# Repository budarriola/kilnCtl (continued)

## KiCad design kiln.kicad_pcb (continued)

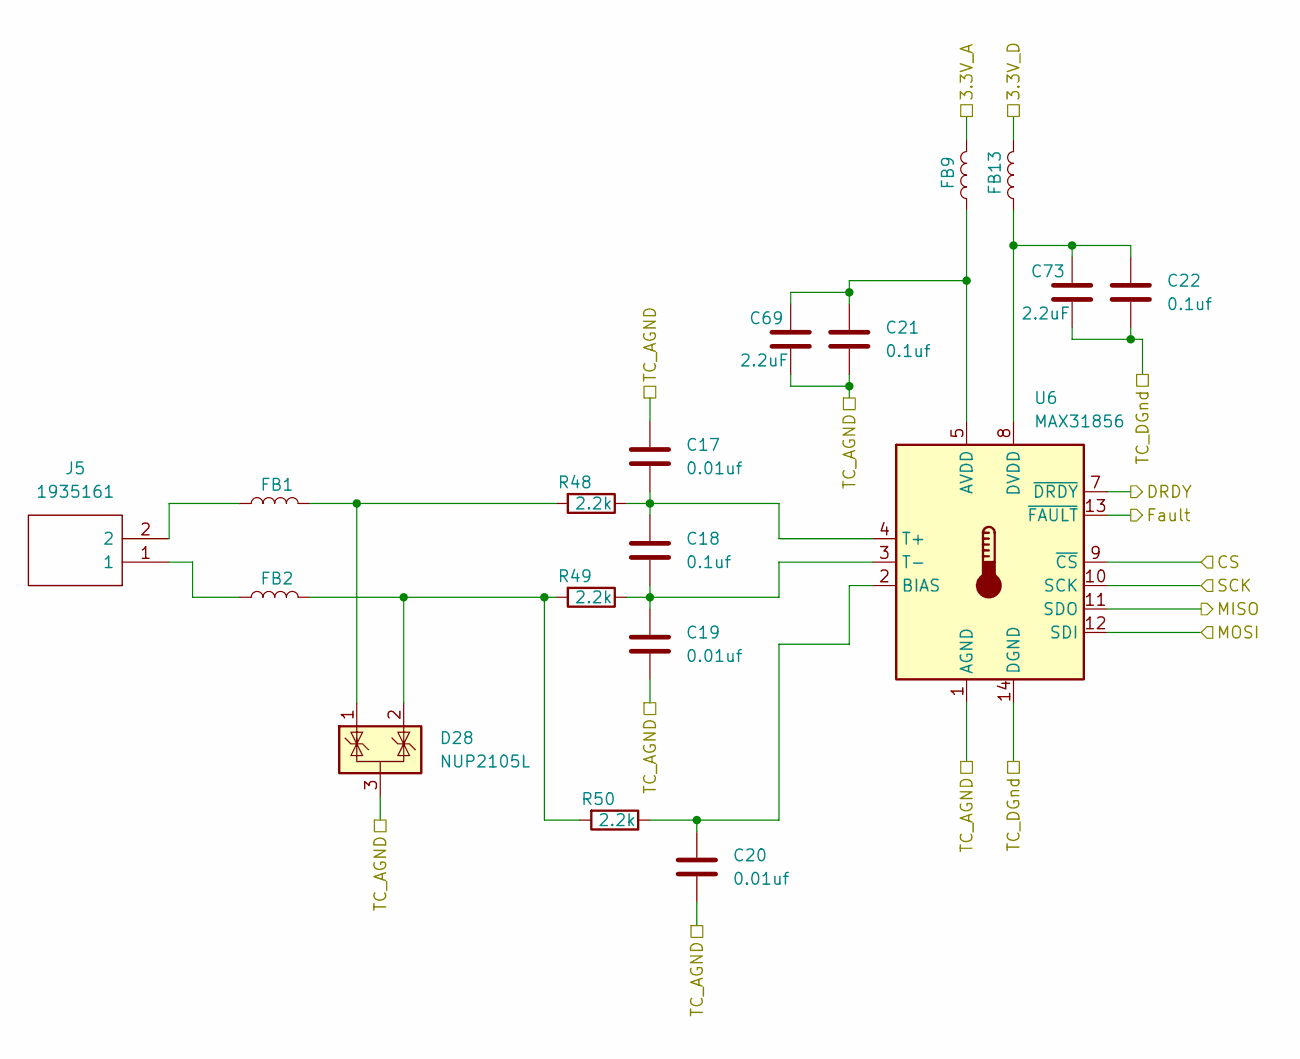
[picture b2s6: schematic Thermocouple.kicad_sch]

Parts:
C17, C19, C20: 0.01uf; C_0402_1005Metric
C18, C21, C22: 0.1uf; C_0402_1005Metric
C69, C73: 2.2uF; C_1206_3216Metric
D28: NUP2105L; SOT-23
FB1, FB2, FB9, FB13: 1.8k; L_0402_1005Metric_Pad0.77x0.64mm_HandSolder
J5: 1935161; Mouser Part Number 651-1935161
R48, R49, R50: 2.2k; R_0402_1005Metric
U6: MAX31856; TSSOP-14_4.4x5mm_P0.65mm

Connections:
3.3v_Safty: FB9.2, FB13.2; also elsewhere on the board
/SaftyProcessor/CLK: U6.10 (SCK); also elsewhere on the board
/SaftyProcessor/CS0: U6.9 (~CS); also elsewhere on the board
/SaftyProcessor/MISO: U6.11 (SDO); also elsewhere on the board
/SaftyProcessor/MOSI: U6.12 (SDI); also elsewhere on the board
/SaftyProcessor/thermoDrdy: U6.7 (~DRDY); also elsewhere on the board
/SaftyProcessor/thermoFault: U6.13 (~FAULT); also elsewhere on the board
GND_Safty: C17.1, C19.2, C20.2, C21.2, C22.2, C69.2, C73.2, D28.3 (A), U6.1 (AGND), U6.14 (DGND); also elsewhere on the board
unnamed: D28.1 (K), FB1.2, R48.2
unnamed: D28.2 (K), FB2.2, R49.2, R50.2
unnamed: FB1.1, J5.2
unnamed: FB2.1, J5.1
unnamed: C21.1, C69.1, FB9.1, U6.5 (AVDD)
unnamed: C20.1, R50.1, U6.2 (BIAS)
unnamed: C22.1, C73.1, FB13.1, U6.8 (DVDD)
unnamed: C17.2, C18.1, R48.1, U6.4 (T+)
unnamed: C18.2, C19.1, R49.1, U6.3 (T-)

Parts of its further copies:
C23, C25, C26, C29, C31, C32, C36, C38, C39: 0.01uf; C_0402_1005Metric
C24, C27, C28, C30, C33, C34, C37, C40, C41: 0.1uf; C_0402_1005Metric
C70, C71, C72, C75, C77, C79: 2.2uF; C_1206_3216Metric
D29, D30, D31: NUP2105L; SOT-23
FB3, FB4, FB5, FB6, FB7, FB8, FB10, FB11, FB12, FB14, FB15, FB16: 1.8k; L_0402_1005Metric_Pad0.77x0.64mm_HandSolder
J6, J7, J9: 1935161; Mouser Part Number 651-1935161
U7, U8, U9: MAX31856; TSSOP-14_4.4x5mm_P0.65mm

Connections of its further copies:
3.3V_Main: FB10.2, FB11.2, FB12.2, FB14.2, FB15.2, FB16.2; also elsewhere on the board
/MainControler/CLK: U7.10 (SCK), U8.10 (SCK), U9.10 (SCK); also elsewhere on the board
/MainControler/CS0: U7.9 (~CS); also elsewhere on the board
/MainControler/CS1: U8.9 (~CS); also elsewhere on the board
/MainControler/CS2: U9.9 (~CS); also elsewhere on the board
/MainControler/MISO: U7.11 (SDO), U8.11 (SDO), U9.11 (SDO); also elsewhere on the board
/MainControler/MOSI: U7.12 (SDI), U8.12 (SDI), U9.12 (SDI); also elsewhere on the board
/MainControler/thermoDrdy_0: U7.7 (~DRDY); also elsewhere on the board
/MainControler/thermoDrdy_1: U8.7 (~DRDY); also elsewhere on the board
/MainControler/thermoDrdy_2: U9.7 (~DRDY); also elsewhere on the board
/MainControler/thermoFault_0: U7.13 (~FAULT); also elsewhere on the board
/MainControler/thermoFault_1: U8.13 (~FAULT); also elsewhere on the board
/MainControler/thermoFault_2: U9.13 (~FAULT); also elsewhere on the board
GND_Main: C23.1, C25.2, C26.2, C27.2, C28.2, C29.1, C31.2, C32.2, C33.2, C34.2, C36.1, C38.2, C39.2, C40.2, C41.2, C70.2, C71.2, C72.2, C75.2, C77.2, C79.2, D29.3 (A), D30.3 (A), D31.3 (A), U7.1 (AGND), U7.14 (DGND), U8.1 (AGND), U8.14 (DGND), U9.1 (AGND), U9.14 (DGND); also elsewhere on the board
unnamed 77: D29.1 (K), FB3.2; also elsewhere on the board
unnamed 78: D29.2 (K), FB4.2; also elsewhere on the board
unnamed 79: D30.1 (K), FB5.2; also elsewhere on the board
unnamed 80: D30.2 (K), FB6.2; also elsewhere on the board
unnamed 81: D31.1 (K), FB7.2; also elsewhere on the board
unnamed 82: D31.2 (K), FB8.2; also elsewhere on the board
unnamed: FB3.1, J6.2
unnamed: FB4.1, J6.1
unnamed: FB5.1, J7.2
unnamed: FB6.1, J7.1
unnamed: FB7.1, J9.2
unnamed: FB8.1, J9.1
unnamed: C27.1, C70.1, FB10.1, U7.5 (AVDD)
unnamed 155: C26.1, U7.2 (BIAS); also elsewhere on the board
unnamed: C28.1, C75.1, FB14.1, U7.8 (DVDD)
unnamed 157: C23.2, C24.1, U7.4 (T+); also elsewhere on the board
unnamed 158: C24.2, C25.1, U7.3 (T-); also elsewhere on the board
unnamed: C33.1, C71.1, FB11.1, U8.5 (AVDD)
unnamed 160: C32.1, U8.2 (BIAS); also elsewhere on the board
unnamed: C34.1, C77.1, FB15.1, U8.8 (DVDD)
unnamed 162: C29.2, C30.1, U8.4 (T+); also elsewhere on the board
unnamed 163: C30.2, C31.1, U8.3 (T-); also elsewhere on the board
unnamed: C40.1, C72.1, FB12.1, U9.5 (AVDD)
unnamed 165: C39.1, U9.2 (BIAS); also elsewhere on the board
unnamed: C41.1, C79.1, FB16.1, U9.8 (DVDD)
unnamed 167: C36.2, C37.1, U9.4 (T+); also elsewhere on the board
unnamed 168: C37.2, C38.1, U9.3 (T-); also elsewhere on the board

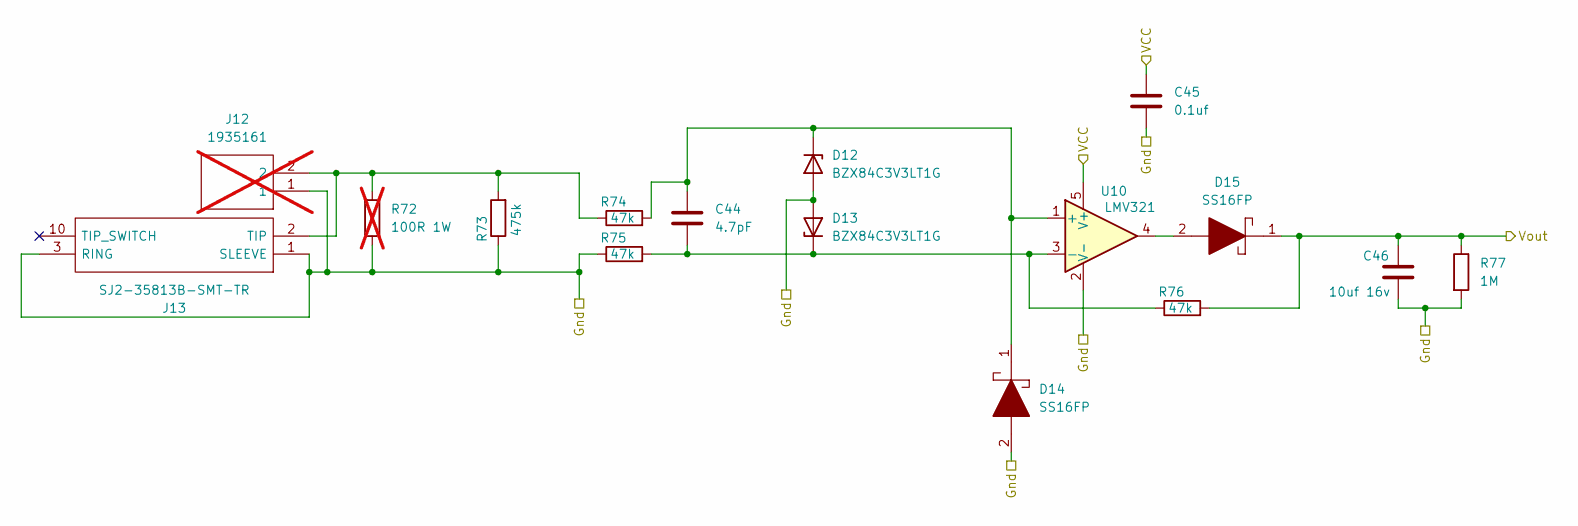
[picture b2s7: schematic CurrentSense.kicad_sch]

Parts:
C44: 4.7pF; C_0402_1005Metric
C45: 0.1uf; C_0402_1005Metric
C46: 10uf 16v; C_0805_2012Metric
D12, D13: BZX84C3V3LT1G; SOT-23
D14, D15: SS16FP; SS12FP; Mouser Part Number 512-SS16FP
J12: 1935161; Mouser Part Number 651-1935161; not fitted
J13: SJ2-35813B-SMT-TR; SJ235813BSMTTR; Mouser Part Number 490-SJ2-35813BSMT-TR
R72: 100R 1W; R_2512_6332Metric; not fitted
R73: 475k; R_0402_1005Metric
R74, R75, R76: 47k; R_0402_1005Metric
R77: 1M; R_0402_1005Metric
U10: LMV321; SOT-353_SC-70-5

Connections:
3.3v_Safty: C45.1, U10.5 (V+); also elsewhere on the board
/SaftyProcessor/Current1: C46.1, D15.1, R76.2, R77.1; also elsewhere on the board
GND_Safty: C45.2, C46.2, D12.1 (A), D13.1 (A), D14.2, J12.1, J13.1 (SLEEVE), J13.3 (RING), R72.2, R73.1, R75.1, R77.2, U10.2 (V-); also elsewhere on the board
unnamed: C44.1, D12.3 (K), D14.1, R74.2, U10.1 (+)
unnamed: C44.2, D13.3 (K), R75.2, R76.1, U10.3 (-)
unnamed: D15.2, U10.4
unnamed: J12.2, J13.2 (TIP), R72.1, R73.2, R74.1

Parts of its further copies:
C47, C50: 4.7pF; C_0402_1005Metric
C48, C51: 0.1uf; C_0402_1005Metric
C49, C52: 10uf 16v; C_0805_2012Metric
D16, D17, D20, D21: BZX84C3V3LT1G; SOT-23
D18, D19, D22, D23: SS16FP; SS12FP; Mouser Part Number 512-SS16FP
J14, J16: 1935161; Mouser Part Number 651-1935161; not fitted
J15, J17: SJ2-35813B-SMT-TR; SJ235813BSMTTR; Mouser Part Number 490-SJ2-35813BSMT-TR
R78, R84: 100R 1W; R_2512_6332Metric; not fitted
R79, R85: 475k; R_0402_1005Metric
R80, R81, R82, R86, R87, R88: 47k; R_0402_1005Metric
R83, R89: 1M; R_0402_1005Metric
U11, U12: LMV321; SOT-353_SC-70-5

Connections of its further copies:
3.3v_Safty: C48.1, C51.1, U11.5 (V+), U12.5 (V+); also elsewhere on the board
/SaftyProcessor/Current2: C49.1, D19.1, R82.2, R83.1; also elsewhere on the board
/SaftyProcessor/Current3: C52.1, D23.1, R88.2, R89.1; also elsewhere on the board
GND_Safty: C48.2, C49.2, C51.2, C52.2, D16.1 (A), D17.1 (A), D18.2, D20.1 (A), D21.1 (A), D22.2, J14.1, J15.1 (SLEEVE), J15.3 (RING), J16.1, J17.1 (SLEEVE), J17.3 (RING), R78.2, R79.1, R81.1, R83.2, R84.2, R85.1, R87.1, R89.2, U11.2 (V-), U12.2 (V-); also elsewhere on the board
unnamed: C47.1, D16.3 (K), D18.1, R80.2, U11.1 (+)
unnamed: C47.2, D17.3 (K), R81.2, R82.1, U11.3 (-)
unnamed: D19.2, U11.4
unnamed: C50.1, D20.3 (K), D22.1, R86.2, U12.1 (+)
unnamed: C50.2, D21.3 (K), R87.2, R88.1, U12.3 (-)
unnamed: D23.2, U12.4
unnamed: J14.2, J15.2 (TIP), R78.1, R79.2, R80.1
unnamed: J16.2, J17.2 (TIP), R84.1, R85.2, R86.1

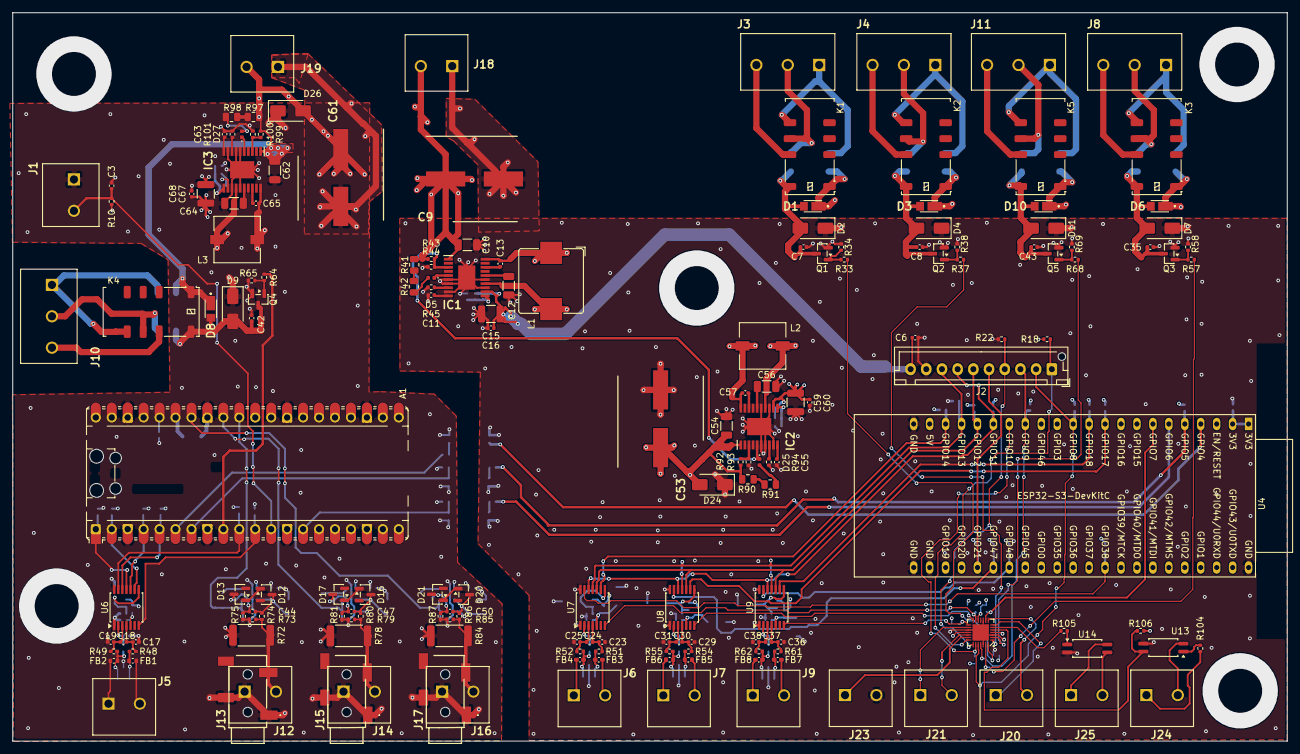
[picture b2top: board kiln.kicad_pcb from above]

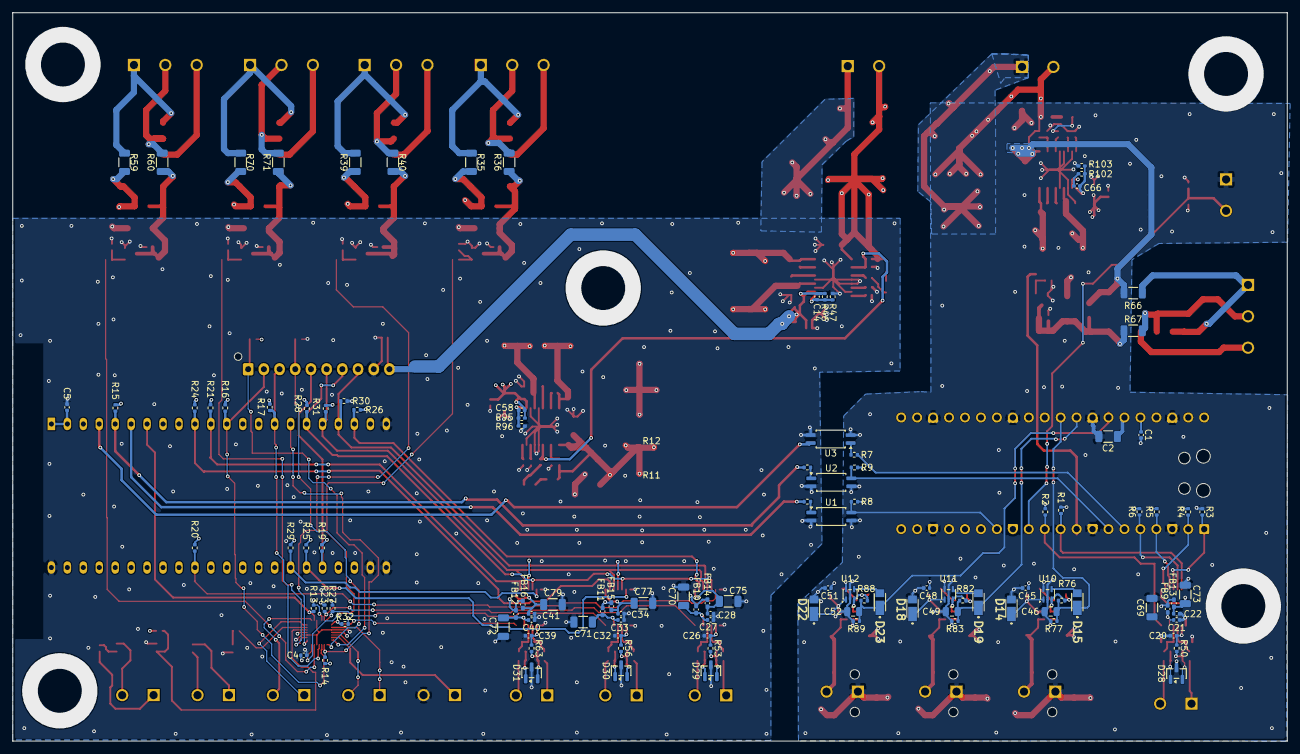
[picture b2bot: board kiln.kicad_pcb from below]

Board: 4 copper layers, 203.0 x 116.0 mm, 284 parts (112 on the bottom side), 169 nets.

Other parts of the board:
R51, R52, R53, R54, R55, R56, R61, R62, R63: 2k; R_0402_1005Metric

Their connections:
unnamed 77: R51.2; also elsewhere on the board
unnamed 78: R52.2, R53.2; also elsewhere on the board
unnamed 79: R54.2; also elsewhere on the board
unnamed 80: R55.2, R56.2; also elsewhere on the board
unnamed 81: R61.2; also elsewhere on the board
unnamed 82: R62.2, R63.2; also elsewhere on the board
unnamed 155: R53.1; also elsewhere on the board
unnamed 157: R51.1; also elsewhere on the board
unnamed 158: R52.1; also elsewhere on the board
unnamed 160: R56.1; also elsewhere on the board
unnamed 162: R54.1; also elsewhere on the board
unnamed 163: R55.1; also elsewhere on the board
unnamed 165: R63.1; also elsewhere on the board
unnamed 167: R61.1; also elsewhere on the board
unnamed 168: R62.1; also elsewhere on the board

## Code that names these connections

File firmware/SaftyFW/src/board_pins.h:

// board_pins.h -- the RP2040 GPIO/ADC map for A1 on the kilnCtl main board.
// Single source of truth so no task file re-derives a pin number from memory.
// Traced and verified in docs/HARDWARE.md section "Pico I/O map" (also ARCHITECTURE.md
// section 3's module table) -- if this disagrees with either, the docs win and this
// file is wrong.
//
// Deliberately a plain header, not a driver: it holds only pin numbers, not
// initialisation code, so every hardware-owner task can include it without
// pulling in another task's setup.
#ifndef SAFTYFW_BOARD_PINS_H
#define SAFTYFW_BOARD_PINS_H

// --- SPI0: MAX31856 thermocouple ADC (spi_owner) ---------------------------
#define SAFTYFW_PIN_SPI0_MISO   0   // GPIO0, SPI0 RX from the MAX31856
#define SAFTYFW_PIN_SPI0_CS0    1   // GPIO1, MAX31856 ~CS, active low, driven as plain GPIO
#define SAFTYFW_PIN_SPI0_SCK    2   // GPIO2, SPI0 SCK
#define SAFTYFW_PIN_SPI0_MOSI   3   // GPIO3, SPI0 TX

// --- UART1: the opto-isolated link to the ESP (uart_owner / link_task) -----
// NEVER referenced from safety_core.c or relay_owner.c -- see the CI grep
// check in tools/check_isolation.ps1.
#define SAFTYFW_PIN_UART1_TX    4   // GP4, PicoTx -> R7 -> U3 -> ESP RX (GPIO4)
#define SAFTYFW_PIN_UART1_RX    5   // GP5, PicoRx <- U2 <- R12 <- ESP TX (GPIO5)

// --- The safety actuator (relay_owner). The ONLY code that may write this. -
#define SAFTYFW_PIN_RELAY       6   // GPIO6, saftyRelay -> Q4 gate -> K4 coil. High = energized.

// --- I2C0: wired to J7 but nothing answers today. Left uninitialised. ------
#define SAFTYFW_PIN_I2C0_SDA    7   // GPIO7
#define SAFTYFW_PIN_I2C0_SCL    8   // GPIO8

// --- Discretes (discrete_task) ----------------------------------------------
// GPIO9: ACTIVE HIGH for stop. R10 1k pull-up + C3 noise cap; normally-closed
// contact to GND_Safty, so LOW = healthy, HIGH = pressed/broken/unfitted.
// docs/HARDWARE.md section 5 forbids inverting this in firmware.
#define SAFTYFW_PIN_ESTOP       9
#define SAFTYFW_PIN_MAIN_FAULT  10  // GPIO10, U1 collector, active low

// --- Thermocouple front end (thermo_task, via spi_owner) -------------------
#define SAFTYFW_PIN_THERMO_FAULT 11 // GPIO11, MAX31856 ~FAULT, active low
#define SAFTYFW_PIN_THERMO_DRDY  12 // GPIO12, MAX31856 ~DRDY, active low, real IRQ (Phase 3)

// --- Current sense (current_task, via adc_owner) ----------------------------
// RP2040 SAR ADC input numbers, not GPIO numbers -- adc_select_input() takes
// these directly. GPIO26/27/28 must still be adc_gpio_init()'d (ARCHITECTURE.md
// section 8: "adc_gpio_init() disables the digital functions").
#define SAFTYFW_PIN_ADC0_GPIO    26 // GPIO26, ADC0, Current1
#define SAFTYFW_PIN_ADC1_GPIO    27 // GPIO27, ADC1, Current2
#define SAFTYFW_PIN_ADC2_GPIO    28 // GPIO28, ADC2, Current3
#define SAFTYFW_ADC_CH_CURRENT1  0
#define SAFTYFW_ADC_CH_CURRENT2  1
#define SAFTYFW_ADC_CH_CURRENT3  2
// ADC3 (GPIO29) reads VSYS/3 on a standard Pico -- USELESS here, VSYS is
// unconnected on this board (docs/HARDWARE.md section 6). Do not sample it.
// ADC4 is the internal die temperature sensor -- a free sanity check
// (ARCHITECTURE.md section 8), not part of this phase's skeleton.

// --- Console UART0, debug-probe bridge only (see docs/ARCHITECTURE.md sec 1)
// UART1 is taken by the isolated link, so the console/RTT-adjacent bench path
// uses UART0 on the one free pin pair this board has.
//
// CORRECTED 2026-08-21: these two were swapped relative to the silicon.
// RP2040 IO_BANK0 funcsel tables (pico-sdk
// src/rp2040/hardware_regs/include/hardware/regs/io_bank0.h) are explicit:
// GPIO16's funcsel 2 is UART0_TX, GPIO17's funcsel 2 is UART0_RX -- there is
// no funcsel on GPIO16 that produces UART0_RX or vice versa, so the Pico
// cannot be configured the other way regardless of what a #define says. This
// matches docs/HARDWARE.md section 7b's table (GP16 -> probe RX / Pico
// UART0 TX, GP17 -> probe TX / Pico UART0 RX), which was already correct;
// only this header disagreed with it.
#define SAFTYFW_PIN_UART0_TX     16 // GP16, Pico UART0 TX -> probe's RX
#define SAFTYFW_PIN_UART0_RX     17 // GP17, Pico UART0 RX <- probe's TX

// --- Heartbeat LED (watchdog_task), TODO.md Phase 2 "physical heartbeat" ---
// GPIO25 is NOT part of A1's own schematic/net list above -- it is never
// routed off the Pico module, so it has no entry in docs/HARDWARE.md's I/O
// map the way every other pin here does. It is real hardware nonetheless:
// docs/HARDWARE.md section 2 confirms A1 is `PICO_BOARD=pico` (a stock
// Raspberry Pi Pico module, not pico_w/pico2/a custom board file), and on
// that stock module GPIO25 is hard-wired module-side to the Pico's own
// onboard LED (pico-sdk's PICO_DEFAULT_LED_PIN for `PICO_BOARD=pico`) --
// unlike GPIO0-13/16/17/26-28 above, nothing on A1's board needs to agree
// with this pin for it to work, so there is no "check the schematic" step
// left to do here the way there was for every other constant in this file.
#define SAFTYFW_PIN_HEARTBEAT_LED 25 // GP25, Pico module onboard LED, module-internal (no A1 net)

#endif // SAFTYFW_BOARD_PINS_H

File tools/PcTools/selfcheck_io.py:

"""IO task checks.

Part of the selfcheck.py split (pure refactor) -- moved verbatim, no logic
changes. See selfcheck.py's module docstring for the overall map.
"""
from __future__ import annotations

import json
import math
import pathlib
import struct
import sys
import threading
import time

from kilnctrl import devices, pin_overlay
from kilnctrl.protocol import (
    FRAME_DELIM,
    FRAME_ESC,
    Device,
    Frame,
    FrameDecoder,
    FrameError,
    MsgType,
    crc16_ccitt_false,
    stuff,
    unstuff,
)
from kilnctrl.serial_link import list_ports, recommend_port

from selfcheck_common import check, _make_pair, _responder


def io_checks() -> None:
    """IO (SX1509) payload layouts, query flow, and the auto-report push."""
    from kilnctrl.io_expander import IoClient, IoQueryError
    from kilnctrl.protocol import UART_TASK_ID_IO

    print("\n== IO payload layouts (uart_task_ids.h) ==")
    check("task id IO == 2", UART_TASK_ID_IO, 2)
    check("set_relay bytes", devices.io_set_relay(1, True), b"\x01\x01\x01")
    check("set_relay_mask bytes", devices.io_set_relay_mask(0x0F, 0x05), b"\x02\x0f\x05")
    check("set_io bytes", devices.io_set_io(7, False), b"\x03\x07\x00")
    check("set_io_dir bytes", devices.io_set_io_dir(3, True, True), b"\x04\x03\x01\x01")
    check("read request bytes", devices.io_read(), b"\x05")
    check(
        "set_auto_report bytes (u16 LE)",
        devices.io_set_auto_report(500),
        b"\x06" + struct.pack("<H", 500),
    )
    check("all_relays_off bytes", devices.io_all_relays_off(), b"\x07")
    check("sx_write_reg bytes", devices.sx_write_reg(0x0F, 0xA5), b"\x10\x0f\xa5")
    check("sx_read_reg bytes", devices.sx_read_reg(0x10, 2), b"\x11\x10\x02")
    check("sx_set_dir bytes", devices.sx_set_dir(0xFF00), b"\x12\x00\xff")
    check("sx_set_pullup bytes", devices.sx_set_pullup(0x0010), b"\x13\x10\x00")
    check("sx_set_opendrain bytes", devices.sx_set_opendrain(0x0020), b"\x14\x20\x00")
    check(
        "sx_set_debounce bytes (u16 mask then config)",
        devices.sx_set_debounce(0x00F0, 3),
        b"\x15" + struct.pack("<H", 0x00F0) + b"\x03",
    )
    check(
        "sx_set_int_mask bytes (mask u16 then sense u16)",
        devices.sx_set_int_mask(0x00FF, 0x5555),
        b"\x16" + struct.pack("<HH", 0x00FF, 0x5555),
    )
    check("sx_led_driver bytes", devices.sx_led_driver(4, True, 128), b"\x17\x04\x01\x80")
    check("sx_reset bytes", devices.sx_reset(True), b"\x18\x01")
    check("sx_scan bytes", devices.sx_scan(), b"\x19")

    for label, fn in (
        ("relay 0 rejected", lambda: devices.io_set_relay(0, True)),
        ("relay 5 rejected", lambda: devices.io_set_relay(5, True)),
        ("io 8 rejected", lambda: devices.io_set_io(8, True)),
        ("relay mask 0x10 rejected", lambda: devices.io_set_relay_mask(0x10, 0)),
        ("debounce config 8 rejected", lambda: devices.sx_set_debounce(0, 8)),
        ("led pin 16 rejected", lambda: devices.sx_led_driver(16, True)),
        ("sx_read_reg len 17 rejected", lambda: devices.sx_read_reg(0, 17)),
    ):
        try:
            fn()
            check(label, False, True)
        except ValueError:
            check(label, True, True)

    # The relay numbering is the single most dangerous thing on this board to
    # get wrong, so pin the mapping down in a test rather than only in a doc.
    check("Relay1 is K3 on J8", devices.relay_label(1), "Relay1 (K3 -> J8)")
    check("Relay2 is K1 on J3", devices.relay_label(2), "Relay2 (K1 -> J3)")
    check("Relay3 is K2 on J4", devices.relay_label(3), "Relay3 (K2 -> J4)")
    check("Relay4 is K5 on J11", devices.relay_label(4), "Relay4 (K5 -> J11)")
    check("expander pin 8 is DRDY0", devices.expander_pin_name(8), "thermoDrdy_0")
    check("expander pin 15 is LCD_Reset", devices.expander_pin_name(15).startswith("LCD_Reset"), True)

    # READ reply as io_bridge_task() emits it: relays 1+3 on, IO1/IO2 high,
    # DRDY on channel 1, ~INT asserted.
    read_reply = bytes([0x05]) + struct.pack(
        "<HHBBBB", 0x0105, 0xFF00, 0b0101, 0b0000011, 0b010, 0x01
    )
    check("READ reply is 9 bytes", len(read_reply), 9)
    subcommand, state = devices.parse_io_response(read_reply)
    check("classify READ reply", subcommand, 0x05)
    check("relay 1 on", state.relay(1), True)
    check("relay 2 off", state.relay(2), False)
    check("relay 3 on", state.relay(3), True)
    check("io 1 high", state.io_level(1), True)
    check("io 3 low", state.io_level(3), False)
    check("io 1 is an input (dir bit 4)", state.io_is_input(1), False)
    check("io 5 is an input (dir bit 11)", state.io_is_input(5), True)
    check("channel 1 DRDY asserted", state.drdy_asserted(1), True)
    check("channel 0 DRDY idle", state.drdy_asserted(0), False)
    check("~INT asserted", state.int_asserted, True)
    check("I2C did not fail", state.i2c_failed, False)

    reg_reply = bytes([0x11, 0x10, 2, 0xDE, 0xAD])
    subcommand, registers = devices.parse_io_response(reg_reply)
    check("classify SX_READ_REG reply", subcommand, 0x11)
    check("expander register bytes", registers.data, b"\xde\xad")

    scan_reply = bytes([0x19, 1, 0x3E])
    subcommand, found = devices.parse_io_response(scan_reply)
    check("classify SX_SCAN reply", subcommand, 0x19)
    check("scan found the board's expander", found, [0x3E])

    for label, bad in (
        ("empty io reply rejected", b""),
        ("short READ reply rejected", bytes([0x05, 0, 0])),
        ("SX_READ_REG len mismatch rejected", bytes([0x11, 0, 4, 1])),
        ("SX_SCAN count mismatch rejected", bytes([0x19, 3, 0x3E])),
        ("unknown io subcommand rejected", b"\x7f\x00"),
    ):
        try:
            devices.parse_io_response(bad)
            check(label, False, True)
        except devices.IoResponseError:
            check(label, True, True)

    print("\n== IO query flow + auto-report push over the virtual link ==")
    a, _b, host, esp, (esp_inbox,) = _make_pair((UART_TASK_ID_IO,))
    stop = threading.Event()
    writes: list[bytes] = []

    def answer(payload: bytes):
        if payload[0] == 0x05:
            return read_reply
        if payload[0] == 0x11:
            return reg_reply
        if payload[0] == 0x19:
            return scan_reply
        return None

    _responder(stop, esp_inbox, esp, UART_TASK_ID_IO, answer, seen=writes)

    reports: list = []
    client = IoClient(host, on_report=reports.append)
    try:
        state = client.read(timeout=3.0)
        check("live read query", (state.relay(1), state.drdy_asserted(1)), (True, True))
        check("query answer is not mistaken for an auto-report", reports, [])
        check("live scan query", client.scan(timeout=3.0), [0x3E])
        check("live read_reg query", client.read_reg(0x10, 2, timeout=3.0).data, b"\xde\xad")

        from kilnctrl.serial_link import SendResult

        res = client.send(devices.io_set_relay(2, True))
        check("write-style subcommand ACKed", res, SendResult.OK)
        deadline = time.time() + 2.0
        while not writes and time.time() < deadline:
            time.sleep(0.02)
        check("write reached the bridge", writes[:1], [b"\x01\x02\x01"])

        esp.send(
            dst_task=UART_TASK_ID_IO,
            src_task=UART_TASK_ID_IO,
            payload=read_reply,
            dst_device=Device.HOST,
        )
        deadline = time.time() + 2.0
        while not reports and time.time() < deadline:
            time.sleep(0.02)
        check("unsolicited READ detected as an auto-report", len(reports), 1)

        a.drop_next_writes = 100
        host.max_retries = 2
        try:
            client.read(timeout=0.3)
            check("undelivered query raises", False, True)
        except IoQueryError as exc:
            check("undelivered query raises", exc.send_result is not None, True)
    finally:
        stop.set()
        client.close()
        host.disconnect()
        esp.disconnect()
